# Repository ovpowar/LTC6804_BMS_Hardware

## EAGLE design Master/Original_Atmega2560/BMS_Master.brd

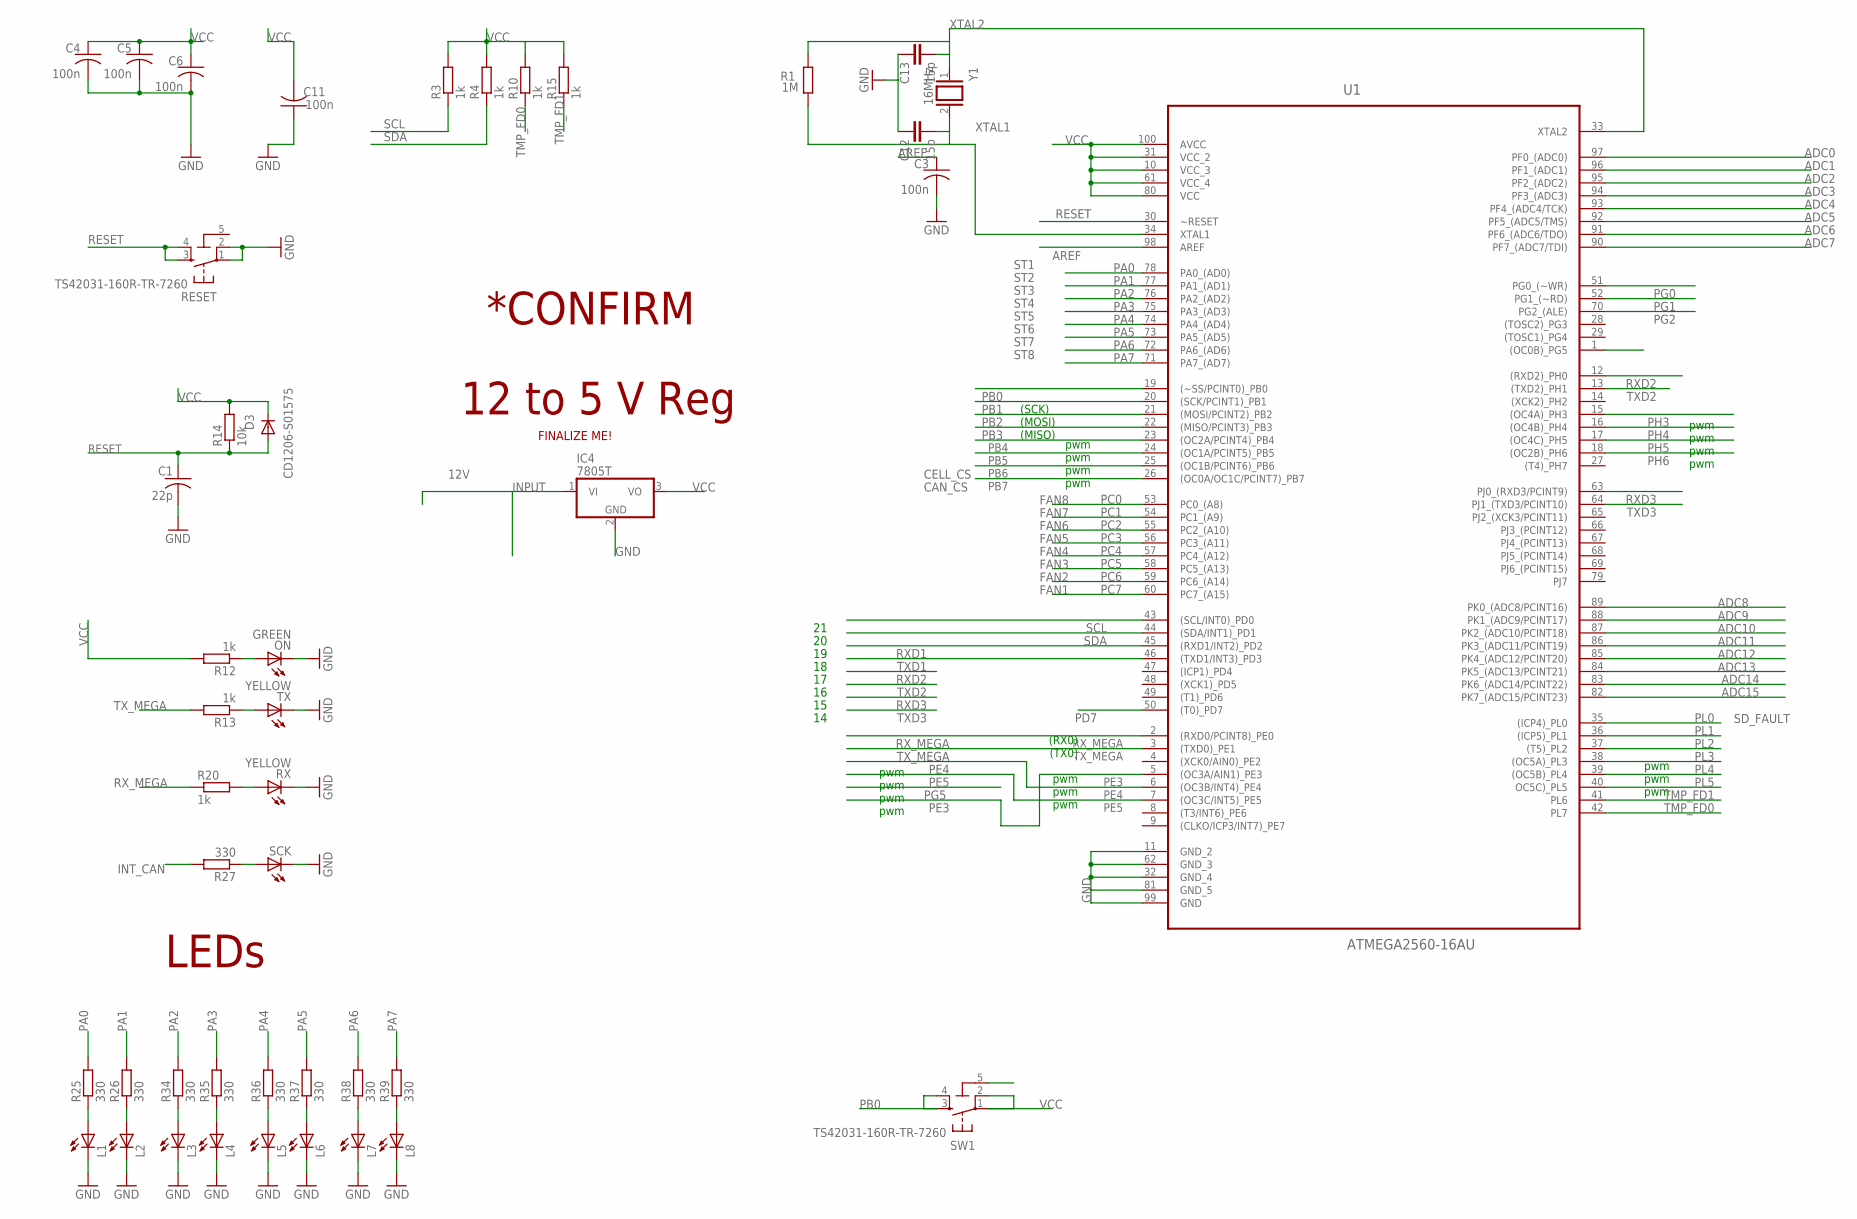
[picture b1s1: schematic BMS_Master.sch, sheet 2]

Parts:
C1: 22p; C1206
C3, C4, C5, C6, C11: 100n; C1206
C12, C13: 15p; C0603-ROUND
D3: CD1206-S01575; MINIMELF
IC4: 7805T; TO220H
L1, L2, L3, L4, L5, L6, L7, L8: LED_E; LED_1206
ON: GREEN; CHIP-LED0805
R1: 1M; R1206W
R3, R4, R10, R15: 1k; R1206
R12, R13, R20: 1k; R0603
R14: 10k; R1206
R25, R26, R27, R34, R35, R36, R37, R38, R39: 330; R0603
RESET: TS42031-160R-TR-7260; TS42
RX: YELLOW; CHIP-LED0805
SCK: LED_E; LED_1206
SW1: TS42031-160R-TR-7260; TS42
TX: YELLOW; CHIP-LED0805
U1: ATMEGA2560-16AU; QFP50P1600X1600X120-100N
Y1: 16MHz; QS

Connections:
5-GND: RESET.5 (5-GND)
ADC0: U1.97 (PF0_(ADC0))
ADC1: U1.96 (PF1_(ADC1))
ADC2: U1.95 (PF2_(ADC2))
ADC3: U1.94 (PF3_(ADC3))
ADC4: U1.93 (PF4_(ADC4/TCK))
ADC5: U1.92 (PF5_(ADC5/TMS))
ADC6: U1.91 (PF6_(ADC6/TDO))
ADC7: U1.90 (PF7_(ADC7/TDI))
ADC8: U1.89 (PK0_(ADC8/PCINT16))
ADC9: U1.88 (PK1_(ADC9/PCINT17))
ADC10: U1.87 (PK2_(ADC10/PCINT18))
ADC11: U1.86 (PK3_(ADC11/PCINT19))
ADC12: U1.85 (PK4_(ADC12/PCINT20))
ADC13: U1.84 (PK5_(ADC13/PCINT21))
ADC14: U1.83 (PK6_(ADC14/PCINT22))
ADC15: U1.82 (PK7_(ADC15/PCINT23))
AREF: C3.1, U1.98 (AREF)
GND: C1.2, C3.2, C4.2, C5.2, C6.2, C11.1, C12.1, C13.1, IC4.2 (GND), L1.C, L2.C, L3.C, L4.C, L5.C, L6.C, L7.C, L8.C, ON.C, RESET.1, RESET.2, RX.C, SCK.C, SW1.5 (5-GND), TX.C, U1.11 (GND_2), U1.32 (GND_4), U1.62 (GND_3), U1.81 (GND_5), U1.99 (GND); also elsewhere on the board
INPUT: IC4.1 (VI); also elsewhere on the board
INT_CAN: R27.2; also elsewhere on the board
unnamed: R20.2, RX.A
unnamed: R13.1, TX.A
unnamed: ON.A, R12.1
unnamed: R27.1, SCK.A
unnamed: L1.A, R25.1
unnamed: L2.A, R26.1
unnamed: L3.A, R34.1
unnamed: L4.A, R35.1
unnamed: L5.A, R36.1
unnamed: L6.A, R37.1
unnamed: L7.A, R38.1
unnamed: L8.A, R39.1
PA0: R25.2, U1.78 (PA0_(AD0))
PA1: R26.2, U1.77 (PA1_(AD1))
PA2: R34.2, U1.76 (PA2_(AD2))
PA3: R35.2, U1.75 (PA3_(AD3))
PA4: R36.2, U1.74 (PA4_(AD4))
PA5: R37.2, U1.73 (PA5_(AD5))
PA6: R38.2, U1.72 (PA6_(AD6))
PA7: R39.2, U1.71 (PA7_(AD7))
PB0: SW1.3, SW1.4, U1.19 ((~SS/PCINT0)_PB0)
PB1: U1.20 ((SCK/PCINT1)_PB1); also elsewhere on the board
PB2: U1.21 ((MOSI/PCINT2)_PB2); also elsewhere on the board
PB3: U1.22 ((MISO/PCINT3)_PB3); also elsewhere on the board
PB4: U1.23 ((OC2A/PCINT4)_PB4); also elsewhere on the board
PB5: U1.24 ((OC1A/PCINT5)_PB5); also elsewhere on the board
PB6: U1.25 ((OC1B/PCINT6)_PB6); also elsewhere on the board
PB7: U1.26 ((OC0A/OC1C/PCINT7)_PB7); also elsewhere on the board
PC0: U1.53 (PC0_(A8))
PC1: U1.54 (PC1_(A9))
PC2: U1.55 (PC2_(A10))
PC3: U1.56 (PC3_(A11))
PC4: U1.57 (PC4_(A12))
PC5: U1.58 (PC5_(A13))
PC6: U1.59 (PC6_(A14))
PC7: U1.60 (PC7_(A15))
PE3: U1.5 ((OC3A/AIN1)_PE3)
PE4: U1.6 ((OC3B/INT4)_PE4)
PE5: U1.7 ((OC3C/INT5)_PE5)
PG0: U1.51 (PG0_(~WR))
PG1: U1.52 (PG1_(~RD))
PG2: U1.70 (PG2_(ALE))
PG5: U1.1 ((OC0B)_PG5)
PH3: U1.15 ((OC4A)_PH3)
PH4: U1.16 ((OC4B)_PH4)
PH5: U1.17 ((OC4C)_PH5)
PH6: U1.18 ((OC2B)_PH6)
PL0: U1.35 ((ICP4)_PL0); also elsewhere on the board
PL1: U1.36 ((ICP5)_PL1); also elsewhere on the board
PL2: U1.37 ((T5)_PL2)
PL3: U1.38 ((OC5A)_PL3)
PL4: U1.39 ((OC5B)_PL4)
PL5: U1.40 (OC5C)_PL5)
RESET: C1.1, D3.A, R14.1, RESET.3, RESET.4, U1.30 (~RESET); also elsewhere on the board
RXD1: U1.45 ((RXD1/INT2)_PD2)
RXD2: U1.12 ((RXD2)_PH0)
RXD3: U1.63 (PJ0_(RXD3/PCINT9))
RX_MEGA: R20.1, U1.2 ((RXD0/PCINT8)_PE0); also elsewhere on the board
SCL: R3.1, U1.43 ((SCL/INT0)_PD0); also elsewhere on the board
SDA: R4.1, U1.44 ((SDA/INT1)_PD1); also elsewhere on the board
TMP_FD0: R10.1, U1.42 (PL7); also elsewhere on the board
TMP_FD1: R15.1, U1.41 (PL6); also elsewhere on the board
TXD1: U1.46 ((TXD1/INT3)_PD3)
TXD2: U1.13 ((TXD2)_PH1)
TXD3: U1.64 (PJ1_(TXD3/PCINT10))
TX_MEGA: R13.2, U1.3 ((TXD0)_PE1); also elsewhere on the board
VCC: C4.1, C5.1, C6.1, C11.2, D3.C, IC4.3 (VO), R3.2, R4.2, R10.2, R12.2, R14.2, R15.2, SW1.1, SW1.2, U1.10 (VCC_3), U1.31 (VCC_2), U1.61 (VCC_4), U1.80 (VCC), U1.100 (AVCC); also elsewhere on the board
XTAL1: C12.2, R1.1, U1.34 (XTAL1), Y1.2
XTAL2: C13.2, R1.2, U1.33 (XTAL2), Y1.1

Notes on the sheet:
pwm
(TX0)
(RX0)
(MISO)
(SCK)
(MOSI)
12 to 5 V Reg
CELL_CS
LEDs
CAN_CS
FINALIZE ME!
SD_FAULT
FAN1
FAN2
FAN3
FAN4
FAN7
FAN5
FAN6
FAN8
ST1
ST2
ST3
ST4
ST5
ST6
ST7
ST8
12V
*CONFIRM

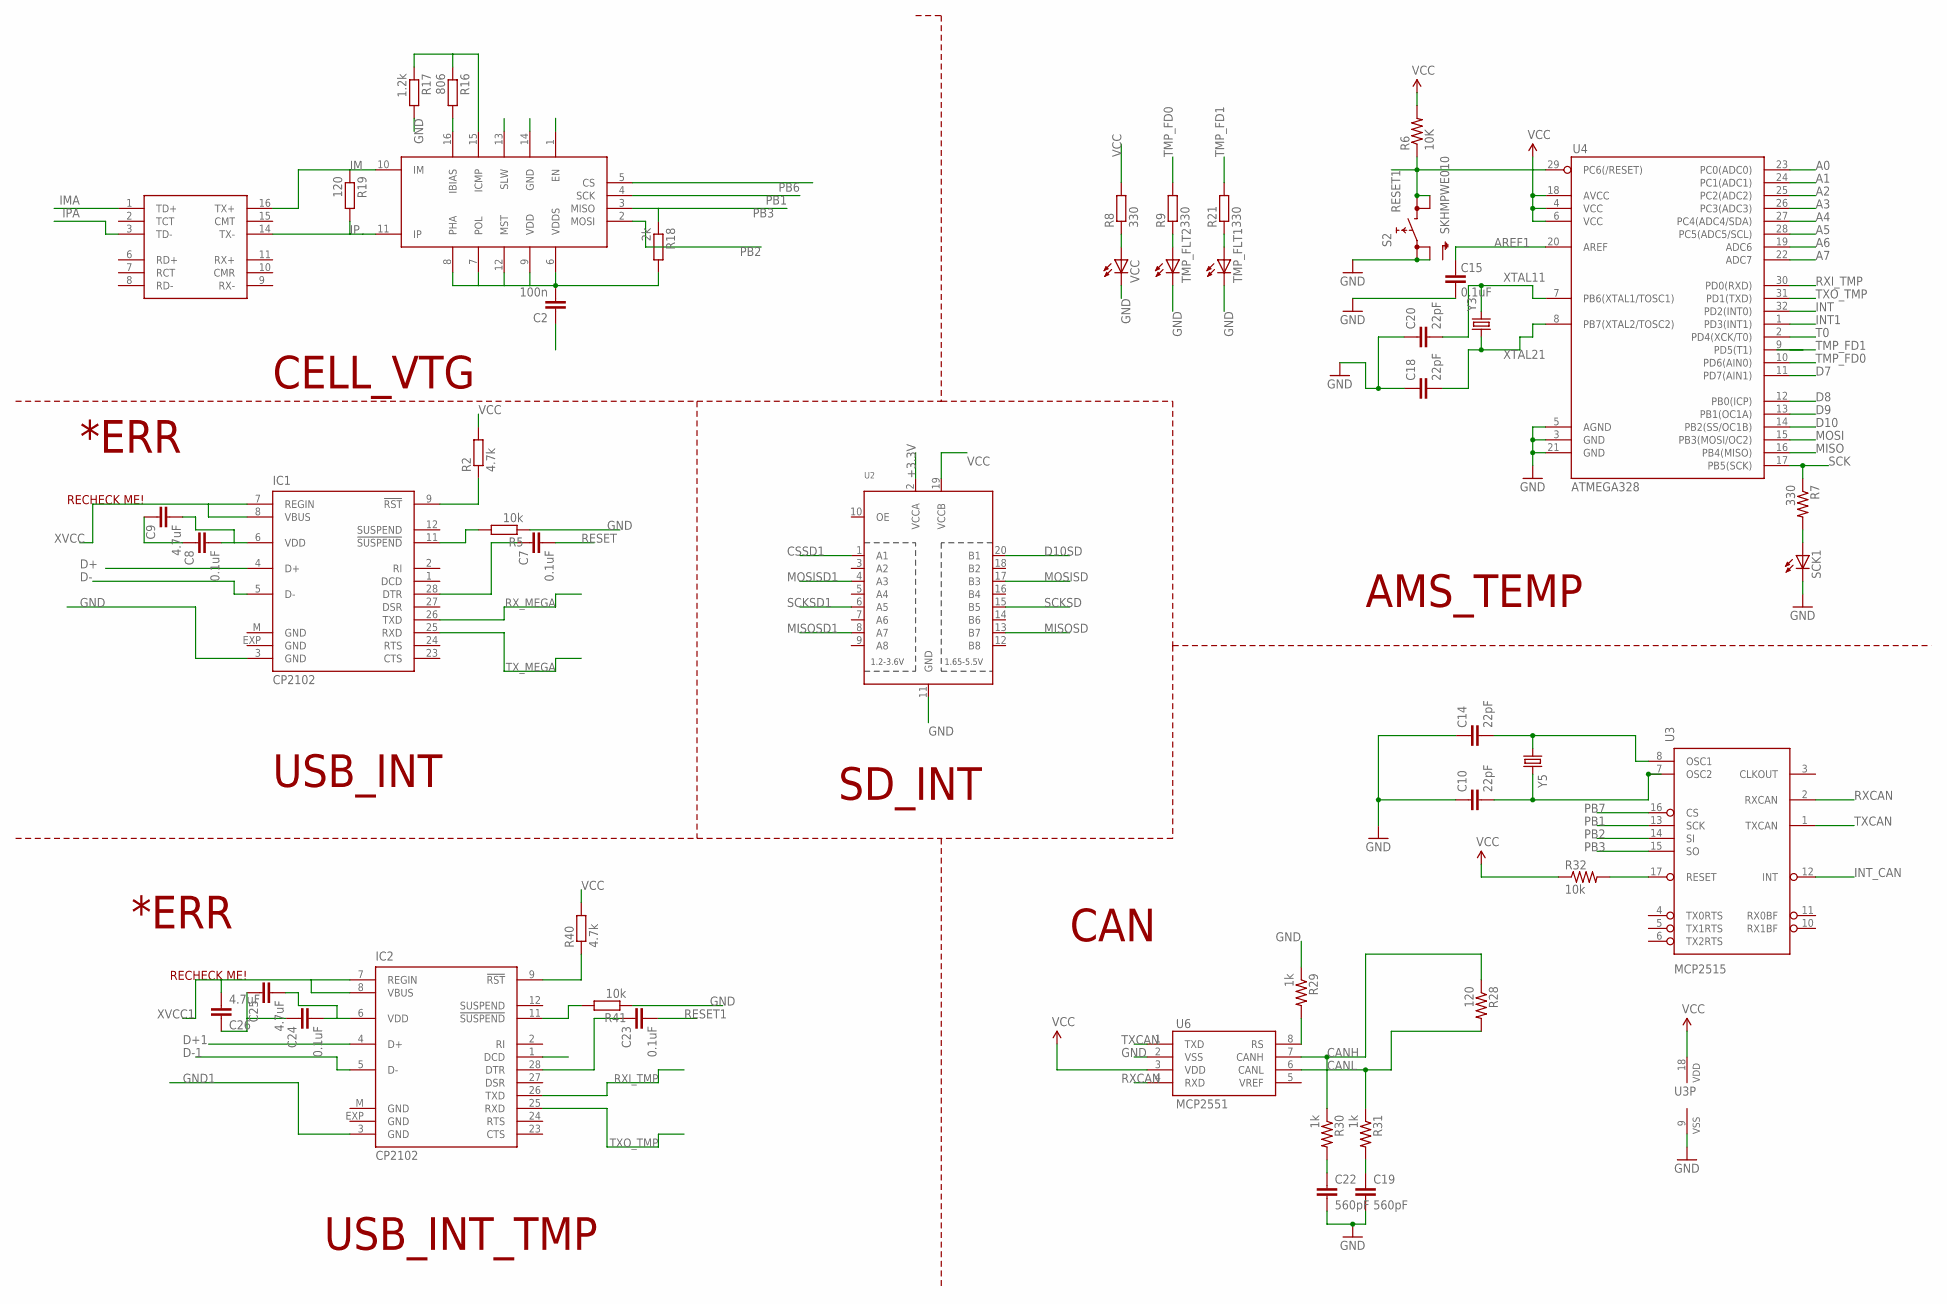
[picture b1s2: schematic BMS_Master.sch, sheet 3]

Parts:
C2: 100n; C1206
C7, C8, C23, C24: 0.1uF; C1206
C9, C25, C26: 4.7uF; C1206
C10, C14, C18, C20: 22pF; 1206
C15: 0.1uF; 1206
C19, C22: 560pF; 1206
IC1, IC2: CP2102; MLP28
R2, R40: 4.7k; R1206
R5, R41: 10k; R1206
R6: 10K; 1206
R7: 330; 0603-RES
R8, R9, R21: 330; R0603
R16: 806; R1206
R17: 1.2k; R1206
R18: 2k; R1206
R19: 120; R1206
R28: 120; 1206
R29, R30, R31: 1k; 1206
R32: 10k; 1206
S2: SKHMPWE010; SKHMPXE010
SCK1: LED_E; LED_1206
TMP_FLT1, TMP_FLT2: LED_E; LED_1206
U2: TXB0108PWR; TSSOP20
U3: MCP2515; SO-18W
U4: ATMEGA328; TQFP32-08
U6: MCP2551; SO08
U$3: LTC6820
U$4: HX1188N; HX1188
VCC: LED_E; LED_1206
Y3, Y5: CRYSTALHC49US; HC49US

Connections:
+3.3V: U2.2 (VCCA); also elsewhere on the board
A0: U4.23 (PC0(ADC0))
A1: U4.24 (PC1(ADC1))
A2: U4.25 (PC2(ADC2))
A3: U4.26 (PC3(ADC3))
A4: U4.27 (PC4(ADC4/SDA))
A5: U4.28 (PC5(ADC5/SCL))
A6: U4.19 (ADC6)
A7: U4.22 (ADC7)
AREF1: C15.2, U4.20 (AREF)
CANH: R28.1, R30.1, U6.7 (CANH); also elsewhere on the board
CANL: R28.2, R31.1, U6.6 (CANL); also elsewhere on the board
CSSD1: U2.1 (A1); also elsewhere on the board
D7: U4.11 (PD7(AIN1)); also elsewhere on the board
D8: U4.12 (PB0(ICP)); also elsewhere on the board
D9: U4.13 (PB1(OC1A)); also elsewhere on the board
D10: U4.14 (PB2(SS/OC1B)); also elsewhere on the board
D10SD: U2.20 (B1); also elsewhere on the board
D+: IC1.4 (D+); also elsewhere on the board
D+1: IC2.4 (D+); also elsewhere on the board
D-: IC1.5 (D-); also elsewhere on the board
D-1: IC2.5 (D-); also elsewhere on the board
GND: C2.1, C8.1, C9.1, C10.1, C14.1, C15.1, C18.1, C19.2, C20.1, C22.2, C24.1, C25.1, C26.1, IC1.3 (GND), IC1.EXP (GND), IC1.M (GND), IC2.EXP (GND), IC2.M (GND), R5.1, R17.2, R29.1, R41.1, S2.1 (1.1), S2.2 (1.2), SCK1.C, TMP_FLT1.C, TMP_FLT2.C, U2.11 (GND), U3.9 (VSS), U4.3 (GND), U4.5 (AGND), U4.21 (GND), U6.2 (VSS), U$3.1 (EN), U$3.13 (SLW), U$3.14 (GND), VCC.C; also elsewhere on the board
GND1: IC2.3 (GND)
IM: R19.1, U$3.10 (IM), U$4.16 (TX+)
IMA: U$4.1 (TD+); also elsewhere on the board
INT: U4.32 (PD2(INT0))
INT1: U4.1 (PD3(INT1))
INT_CAN: U3.12 (INT); also elsewhere on the board
IP: R19.2, U$3.11 (IP), U$4.14 (TX-)
IPA: U$4.3 (TD-); also elsewhere on the board
MISO: U4.16 (PB4(MISO)); also elsewhere on the board
MISOSD: U2.13 (B7); also elsewhere on the board
MISOSD1: U2.8 (A7); also elsewhere on the board
MOSI: U4.15 (PB3(MOSI/OC2)); also elsewhere on the board
MOSISD: U2.17 (B3); also elsewhere on the board
MOSISD1: U2.4 (A3); also elsewhere on the board
unnamed: C14.2, U3.8 (OSC1), Y5.1
unnamed: C10.2, U3.7 (OSC2), Y5.2
unnamed: R16.2, U$3.16 (IBIAS)
unnamed: R16.1, R17.1, U$3.15 (ICMP)
unnamed: R29.2, U6.8 (RS)
unnamed: C22.1, R30.2
unnamed: C19.1, R31.2
unnamed: C7.1, IC1.28 (DTR)
unnamed: IC1.11 (!SUSPEND), R5.2
unnamed: C8.2, C9.2, IC1.6 (VDD)
unnamed: IC1.9 (!RST), R2.1
unnamed: R32.2, U3.17 (RESET)
unnamed: R7.2, SCK1.A
unnamed: R8.1, VCC.A
unnamed: R9.1, TMP_FLT2.A
unnamed: R21.1, TMP_FLT1.A
unnamed: C23.1, IC2.28 (DTR)
unnamed: C24.2, C25.2, IC2.6 (VDD)
unnamed: IC2.9 (!RST), R40.1
unnamed: IC2.11 (!SUSPEND), R41.2
PB1: U3.13 (SCK), U$3.4 (SCK); also elsewhere on the board
PB2: U3.14 (SI), U$3.2 (MOSI); also elsewhere on the board
PB3: R18.1, U3.15 (SO), U$3.3 (MISO); also elsewhere on the board
PB6: U$3.5 (CS); also elsewhere on the board
PB7: U3.16 (CS); also elsewhere on the board
RESET: C7.2; also elsewhere on the board
RESET1: C23.2, R6.1, S2.3 (2.1), S2.4 (2.2), U4.29 (PC6(/RESET)); also elsewhere on the board
RXCAN: U3.2 (RXCAN), U6.4 (RXD)
RXI_TMP: IC2.26 (TXD), U4.30 (PD0(RXD)); also elsewhere on the board
RX_MEGA: IC1.26 (TXD); also elsewhere on the board
SCK: R7.1, U4.17 (PB5(SCK)); also elsewhere on the board
SCKSD: U2.15 (B5); also elsewhere on the board
SCKSD1: U2.6 (A5); also elsewhere on the board
T0: U4.2 (PD4(XCK/T0))
TMP_FD0: R9.2, U4.10 (PD6(AIN0)); also elsewhere on the board
TMP_FD1: R21.2, U4.9 (PD5(T1)); also elsewhere on the board
TXCAN: U3.1 (TXCAN), U6.1 (TXD)
TXO_TMP: IC2.25 (RXD), U4.31 (PD1(TXD)); also elsewhere on the board
TX_MEGA: IC1.25 (RXD); also elsewhere on the board
VCC: C2.2, R2.2, R6.2, R8.2, R18.2, R32.1, R40.2, U2.19 (VCCB), U3.18 (VDD), U4.4 (VCC), U4.6 (VCC), U4.18 (AVCC), U6.3 (VDD), U$3.6 (VDDS), U$3.7 (POL), U$3.8 (PHA), U$3.9 (VDD), U$3.12 (MST); also elsewhere on the board
XTAL11: C20.2, U4.7 (PB6(XTAL1/TOSC1)), Y3.2
XTAL21: C18.2, U4.8 (PB7(XTAL2/TOSC2)), Y3.1
XVCC: IC1.7 (REGIN), IC1.8 (VBUS); also elsewhere on the board
XVCC1: C26.2, IC2.7 (REGIN), IC2.8 (VBUS); also elsewhere on the board

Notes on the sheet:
RECHECK ME!
CELL_VTG
USB_INT
AMS_TEMP
SD_INT
CAN
USB_INT_TMP
*ERR

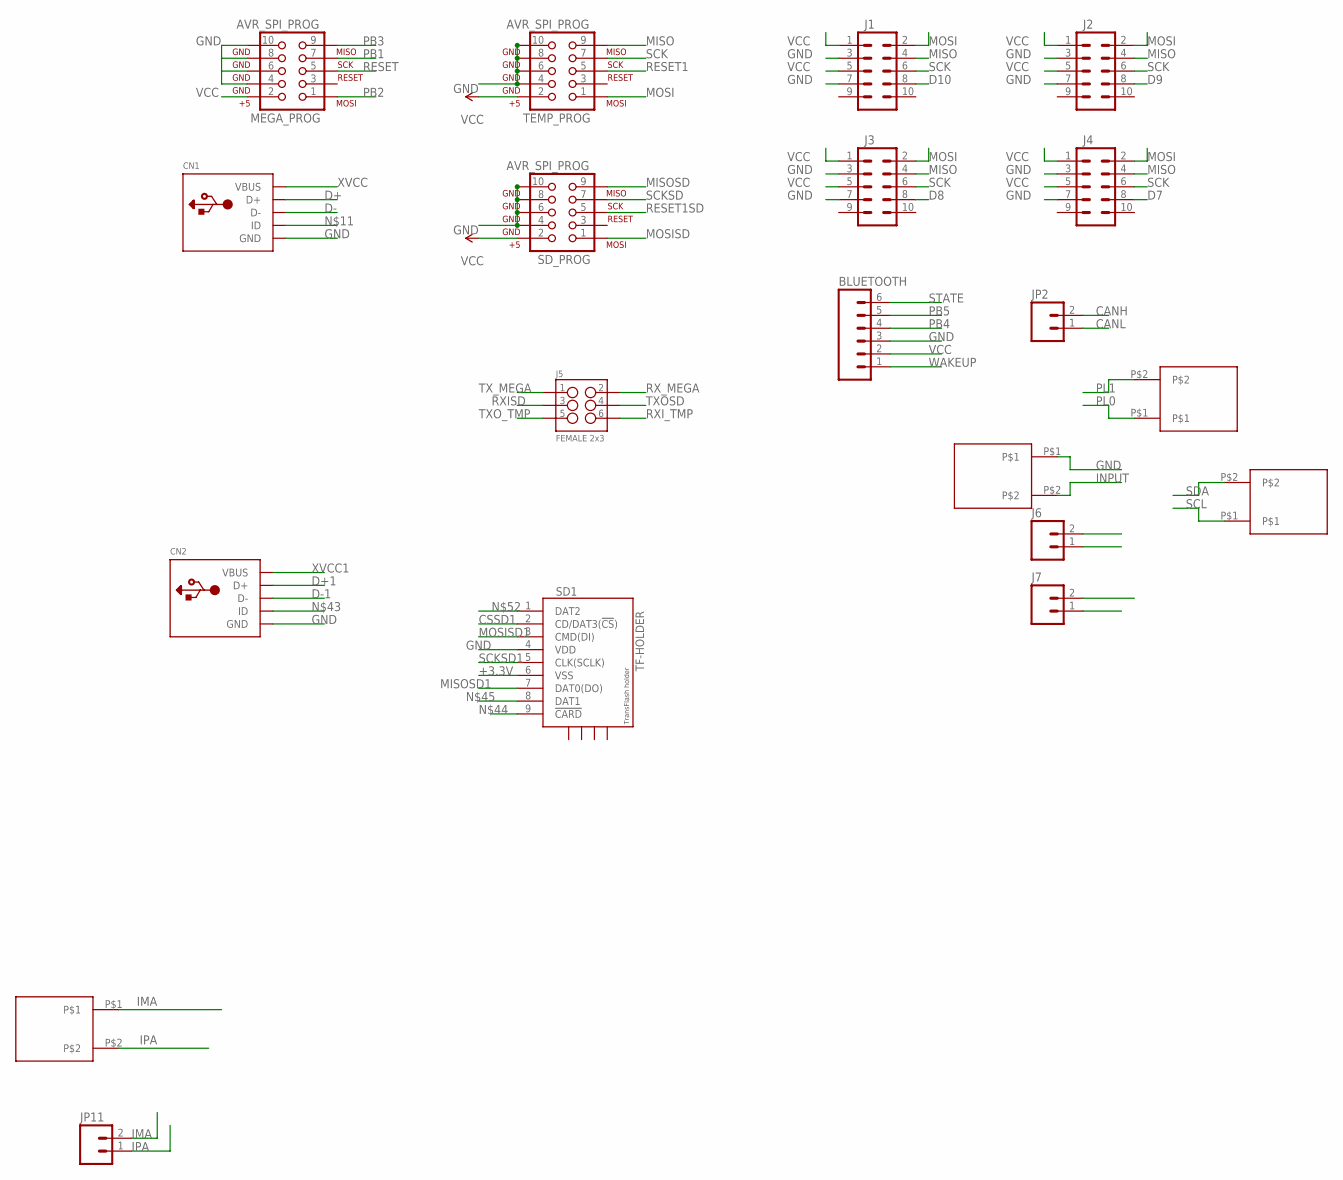
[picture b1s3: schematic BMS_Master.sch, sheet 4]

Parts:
BLUETOOTH: M06SILK_FEMALE_PTH; 1X06
CN1, CN2: USBMINIB; USB-MINIB
J1, J2, J3, J4: M05X2PTH; AVR_ICSP
J5: FEMALE 2x3; 2X3
J6, J7: M02PTH; 1X02
JP2: M02JST-PTH-2; JST-2-PTH
JP11: M02PTH; 1X02
MEGA_PROG: AVR_SPI_PROG; AVR_ICSP
SD1: TF-HOLDER; TF-PULL
SD_PROG: AVR_SPI_PROG; AVR_ICSP
TEMP_PROG: AVR_SPI_PROG; AVR_ICSP
U$1, U$5, U$6, U$7: MOLEX_2_PIN; MOLEX_2PIN

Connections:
+3.3V: SD1.6 (VSS); also elsewhere on the board
CANH: JP2.2; also elsewhere on the board
CANL: JP2.1; also elsewhere on the board
CSSD1: SD1.2 (CD/DAT3(!CS!)); also elsewhere on the board
D7: J4.8; also elsewhere on the board
D8: J3.8; also elsewhere on the board
D9: J2.8; also elsewhere on the board
D10: J1.8; also elsewhere on the board
D+: CN1.D+; also elsewhere on the board
D+1: CN2.D+; also elsewhere on the board
D-: CN1.D-; also elsewhere on the board
D-1: CN2.D-; also elsewhere on the board
GND: BLUETOOTH.3, CN1.GND, CN2.GND, J1.3, J1.7, J2.3, J2.7, J3.3, J3.7, J4.3, J4.7, MEGA_PROG.4, MEGA_PROG.6, MEGA_PROG.8, MEGA_PROG.10, SD1.4 (VDD), SD_PROG.4, SD_PROG.6, SD_PROG.8, SD_PROG.10, TEMP_PROG.4, TEMP_PROG.6, TEMP_PROG.8, TEMP_PROG.10, U$6.P$1; also elsewhere on the board
IMA: JP11.2, U$5.P$1; also elsewhere on the board
INPUT: U$6.P$2; also elsewhere on the board
IPA: JP11.1, U$5.P$2; also elsewhere on the board
MISO: J1.4, J2.4, J3.4, J4.4, TEMP_PROG.9; also elsewhere on the board
MISOSD: SD_PROG.9; also elsewhere on the board
MISOSD1: SD1.7 (DAT0(DO)); also elsewhere on the board
MOSI: J1.2, J2.2, J3.2, J4.2, TEMP_PROG.1; also elsewhere on the board
MOSISD: SD_PROG.1; also elsewhere on the board
MOSISD1: SD1.3 (CMD(DI)); also elsewhere on the board
PB1: MEGA_PROG.7; also elsewhere on the board
PB2: MEGA_PROG.1; also elsewhere on the board
PB3: MEGA_PROG.9; also elsewhere on the board
PB4: BLUETOOTH.4; also elsewhere on the board
PB5: BLUETOOTH.5; also elsewhere on the board
PL0: U$7.P$1; also elsewhere on the board
PL1: U$7.P$2; also elsewhere on the board
RESET: MEGA_PROG.5; also elsewhere on the board
RESET1: TEMP_PROG.5; also elsewhere on the board
RESET1SD: SD_PROG.5; also elsewhere on the board
RXISD: J5.3; also elsewhere on the board
RXI_TMP: J5.6; also elsewhere on the board
RX_MEGA: J5.2; also elsewhere on the board
SCK: J1.6, J2.6, J3.6, J4.6, TEMP_PROG.7; also elsewhere on the board
SCKSD: SD_PROG.7; also elsewhere on the board
SCKSD1: SD1.5 (CLK(SCLK)); also elsewhere on the board
SCL: U$1.P$1; also elsewhere on the board
SDA: U$1.P$2; also elsewhere on the board
STATE: BLUETOOTH.6
TXOSD: J5.4; also elsewhere on the board
TXO_TMP: J5.5; also elsewhere on the board
TX_MEGA: J5.1; also elsewhere on the board
VCC: BLUETOOTH.2, J1.1, J1.5, J2.1, J2.5, J3.1, J3.5, J4.1, J4.5, J6.1, J7.1, MEGA_PROG.2, SD_PROG.2, TEMP_PROG.2; also elsewhere on the board
WAKEUP: BLUETOOTH.1
XVCC: CN1.VBUS, J6.2; also elsewhere on the board
XVCC1: CN2.VBUS, J7.2; also elsewhere on the board

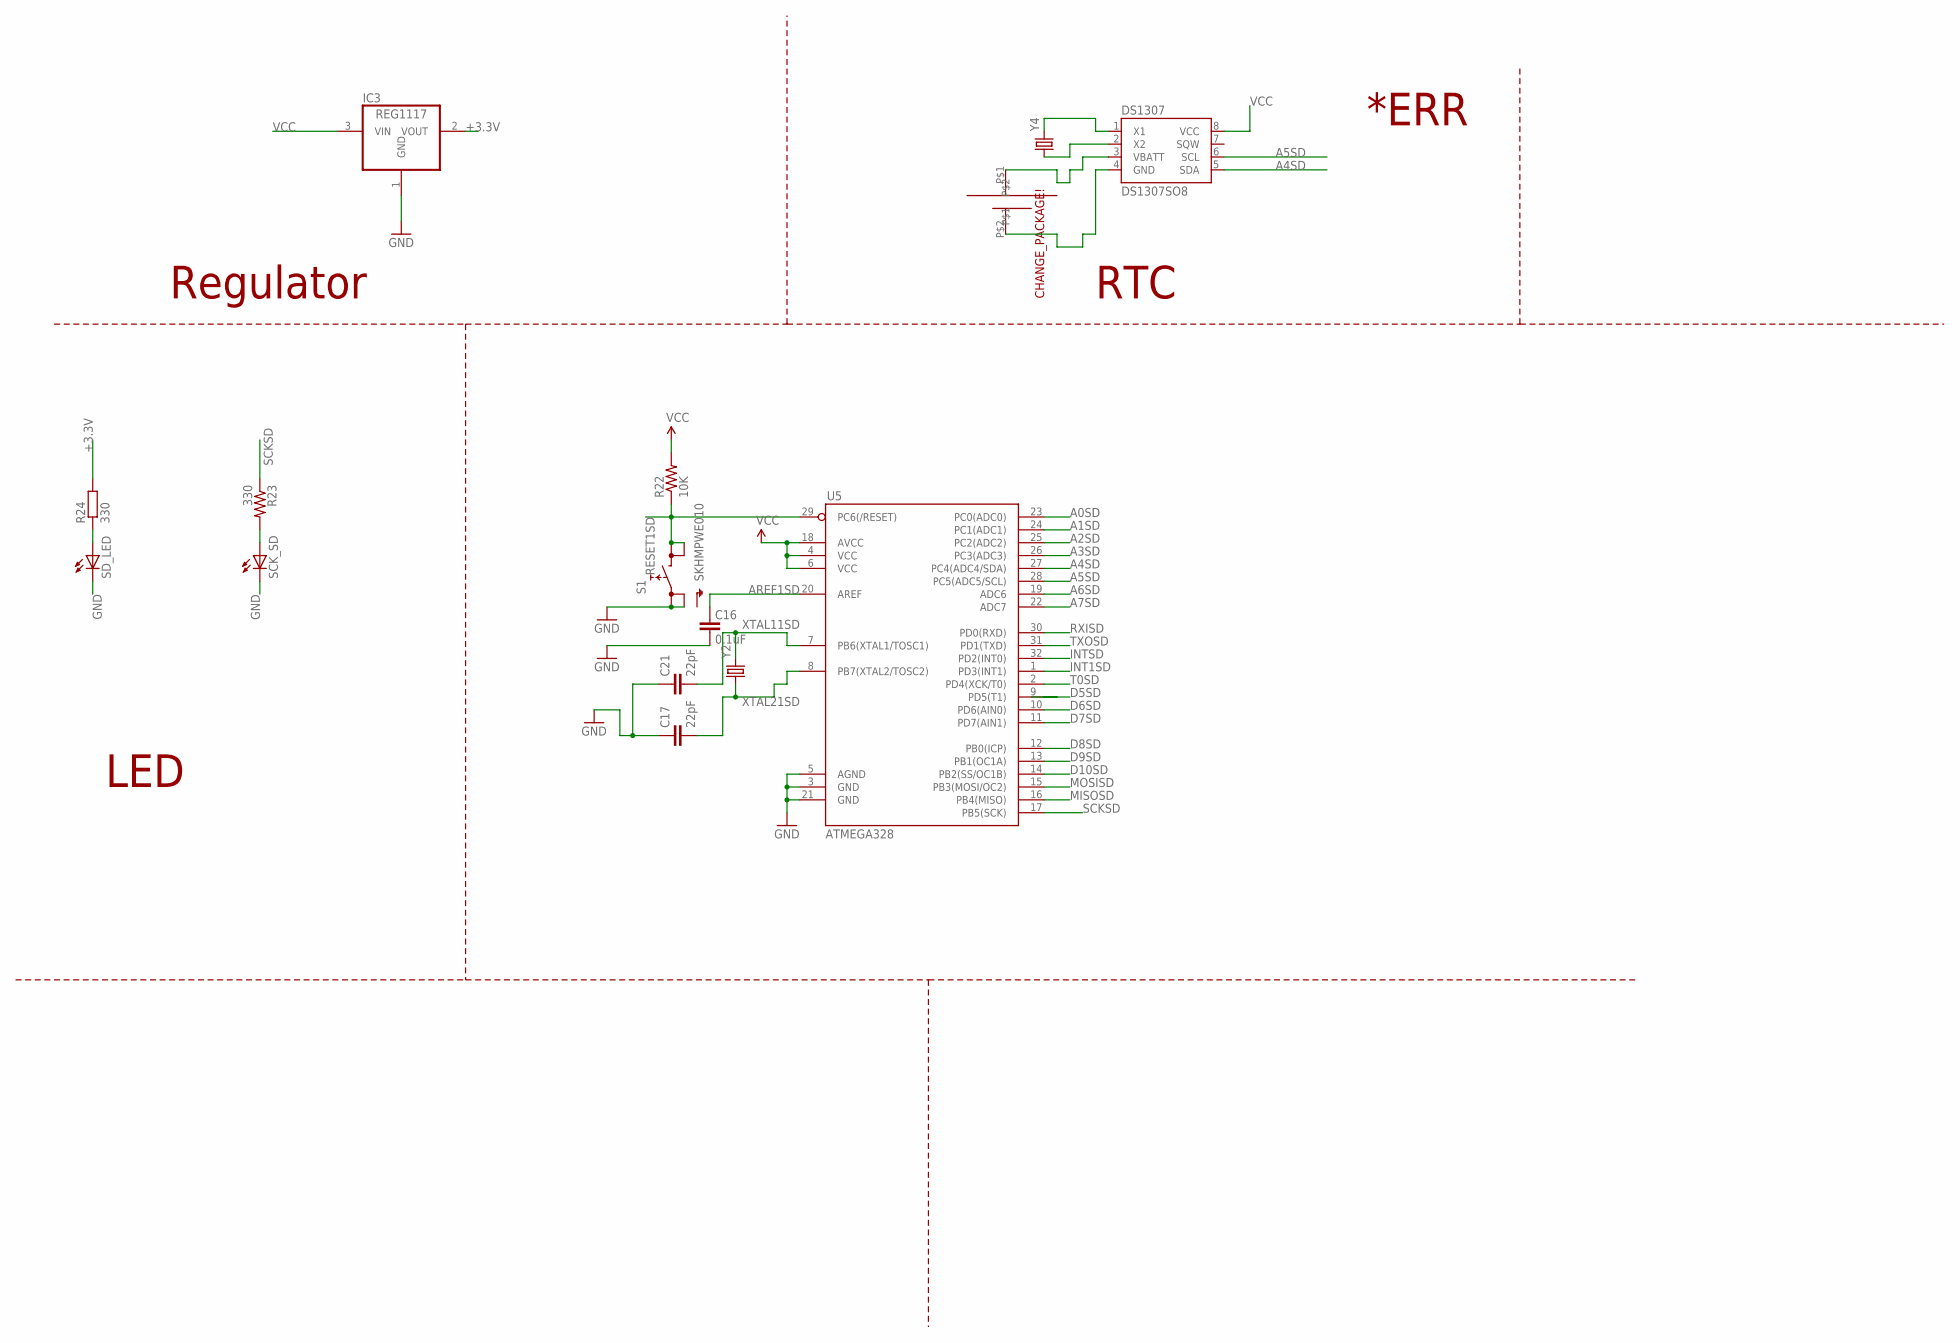
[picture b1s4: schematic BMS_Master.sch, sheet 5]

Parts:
C16: 0.1uF; 1206
C17, C21: 22pF; 1206
CR2032: CR2032
DS1307: DS1307SO8; SO08
IC3: REG1117; SOT223
R22: 10K; 1206
R23: 330; 1206
R24: 330; R1206
S1: SKHMPWE010; SKHMPXE010
SCK_SD: LED_E; LED_1206
SD_LED: LED_E; LED_1206
U5: ATMEGA328; TQFP32-08
Y2: CRYSTALHC49US; HC49US
Y4: CRYSTAL32-SMD; CRYSTAL-32KHZ-SMD

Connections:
+3.3V: IC3.2 (VOUT), R24.2; also elsewhere on the board
A0SD: U5.23 (PC0(ADC0))
A1SD: U5.24 (PC1(ADC1))
A2SD: U5.25 (PC2(ADC2))
A3SD: U5.26 (PC3(ADC3))
A4SD: DS1307.5 (SDA), U5.27 (PC4(ADC4/SDA))
A5SD: DS1307.6 (SCL), U5.28 (PC5(ADC5/SCL))
A6SD: U5.19 (ADC6)
A7SD: U5.22 (ADC7)
AREF1SD: C16.2, U5.20 (AREF)
D5SD: U5.9 (PD5(T1))
D6SD: U5.10 (PD6(AIN0))
D7SD: U5.11 (PD7(AIN1))
D8SD: U5.12 (PB0(ICP))
D9SD: U5.13 (PB1(OC1A))
D10SD: U5.14 (PB2(SS/OC1B)); also elsewhere on the board
GND: C16.1, C17.1, C21.1, IC3.1 (GND), S1.1 (1.1), S1.2 (1.2), SCK_SD.C, SD_LED.C, U5.3 (GND), U5.5 (AGND), U5.21 (GND); also elsewhere on the board
INT1SD: U5.1 (PD3(INT1))
INTSD: U5.32 (PD2(INT0))
MISOSD: U5.16 (PB4(MISO)); also elsewhere on the board
MOSISD: U5.15 (PB3(MOSI/OC2)); also elsewhere on the board
unnamed: DS1307.1 (X1), Y4.X2 (2)
unnamed: DS1307.2 (X2), Y4.X1 (1)
unnamed: CR2032.P$2, DS1307.4 (GND)
unnamed: R23.2, SCK_SD.A
unnamed: R24.1, SD_LED.A
unnamed: CR2032.P$1, DS1307.3 (VBATT)
RESET1SD: R22.1, S1.3 (2.1), S1.4 (2.2), U5.29 (PC6(/RESET)); also elsewhere on the board
RXISD: U5.30 (PD0(RXD)); also elsewhere on the board
SCKSD: R23.1, U5.17 (PB5(SCK)); also elsewhere on the board
T0SD: U5.2 (PD4(XCK/T0))
TXOSD: U5.31 (PD1(TXD)); also elsewhere on the board
VCC: DS1307.8 (VCC), IC3.3 (VIN), R22.2, U5.4 (VCC), U5.6 (VCC), U5.18 (AVCC); also elsewhere on the board
XTAL11SD: C21.2, U5.7 (PB6(XTAL1/TOSC1)), Y2.2
XTAL21SD: C17.2, U5.8 (PB7(XTAL2/TOSC2)), Y2.1

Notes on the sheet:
LED
Regulator
RTC
CHANGE_PACKAGE!
*ERR

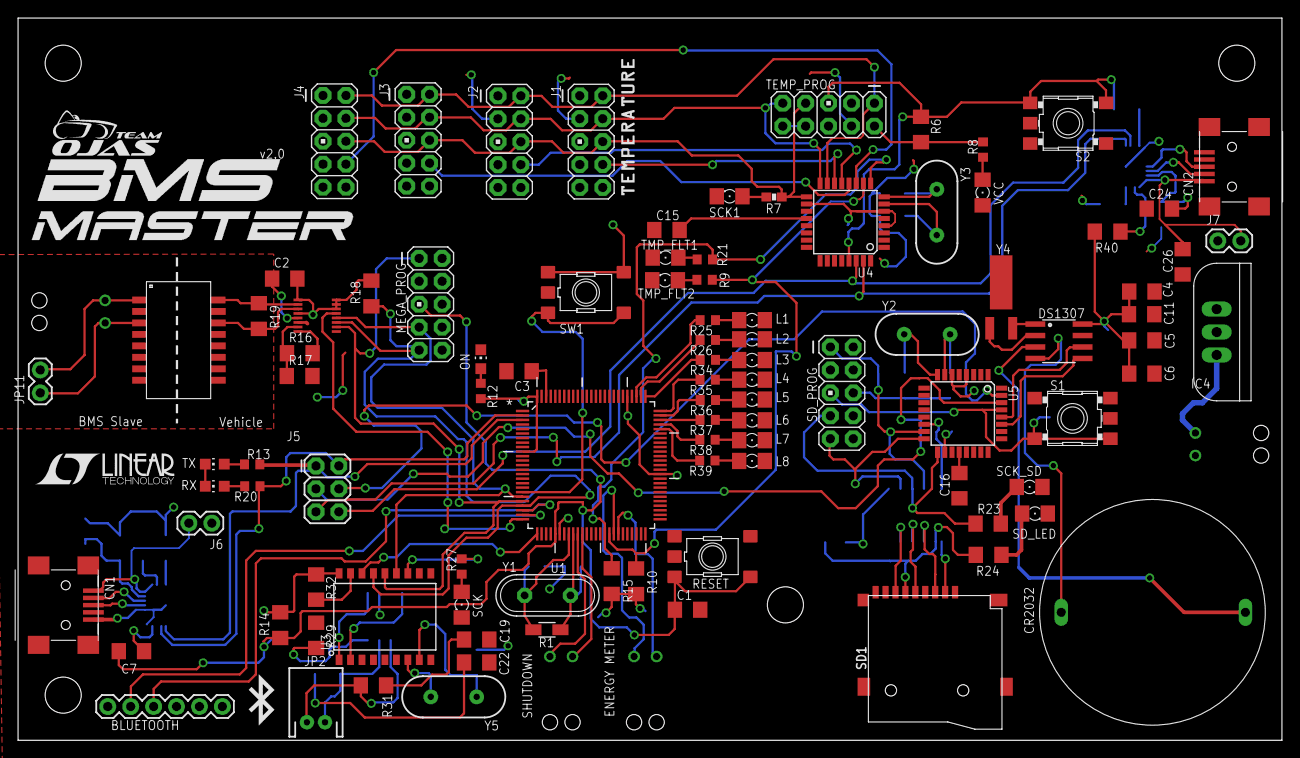
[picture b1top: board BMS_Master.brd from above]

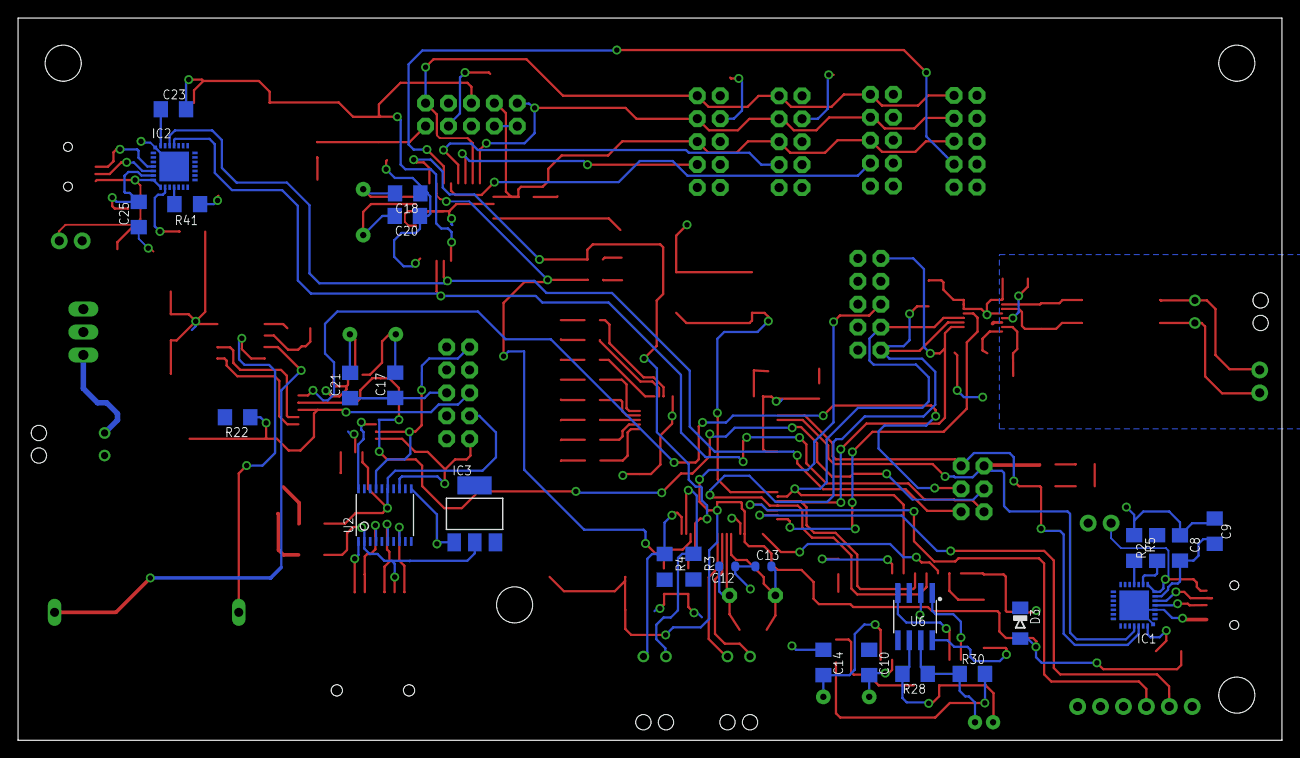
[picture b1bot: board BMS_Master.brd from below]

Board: 2 copper layers, 140.0 x 80.0 mm, 127 parts (26 on the bottom side), 114 nets.

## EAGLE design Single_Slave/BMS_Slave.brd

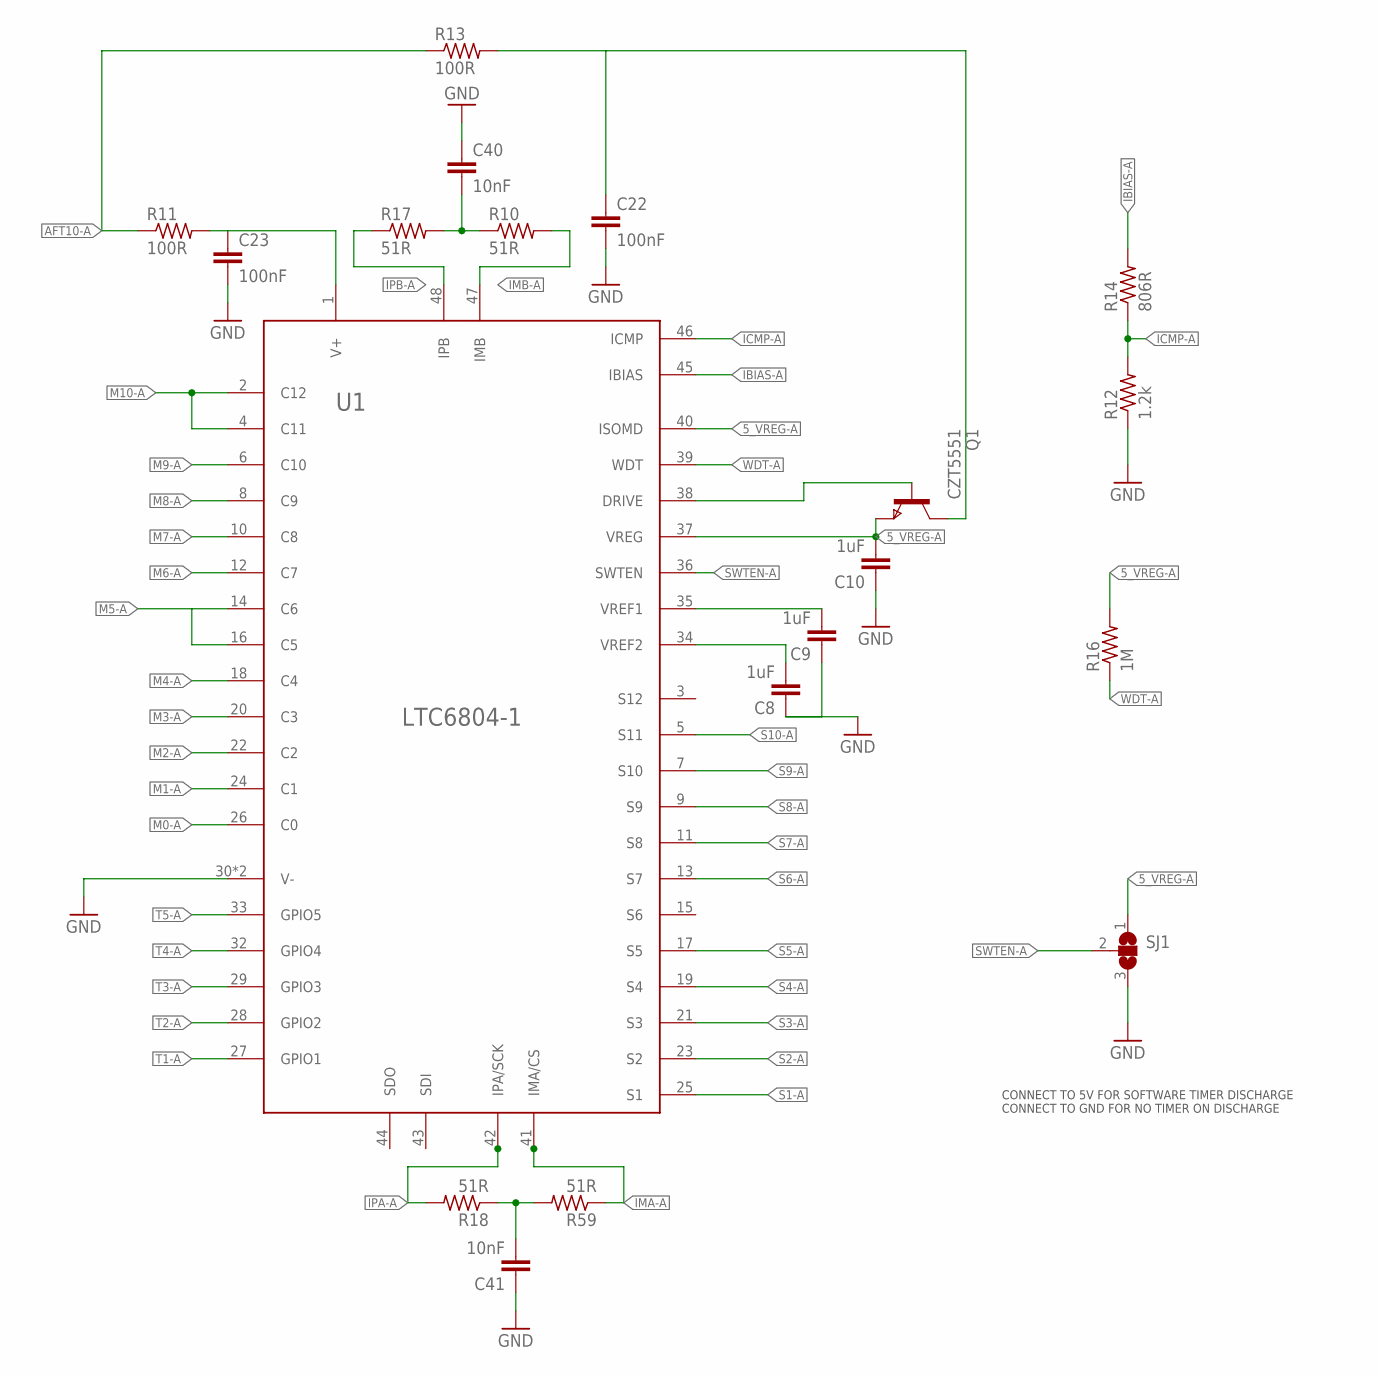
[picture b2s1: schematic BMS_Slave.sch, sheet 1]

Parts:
C8, C9, C10: 1uF; 0603
C22, C23: 100nF; 0805
C40, C41: 10nF; 0805
Q1: CZT5551; SOT223
R10, R17, R18, R59: 51R; 0603
R11, R13: 100R; 0603
R12: 1.2k; 0603
R14: 806R; 0603
R16: 1M; 0603
SJ1: SJ2W; SJ_2
U1: LTC6804; 48-LEAD_SSOP

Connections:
5_VREG-A: C10.P$2 (2), Q1.3 (E), R16.P$2 (2), SJ1.1, U1.37 (VREG), U1.40 (ISOMD); also elsewhere on the board
AFT10-A: R11.P$1 (1), R13.P$1 (1); also elsewhere on the board
GNDA: C8.P$1 (1), C9.P$1 (1), C10.P$1 (1), C22.P$2 (2), C23.P$2 (2), C40.P$1 (1), C41.P$1 (1), R12.P$1 (1), SJ1.3, U1.30 (V-), U1.31 (V-); also elsewhere on the board
IBIAS-A: R14.P$2 (2), U1.45 (IBIAS)
ICMP-A: R12.P$2 (2), R14.P$1 (1), U1.46 (ICMP)
IMA-A: R59.P$1 (1), U1.41 (IMA/CS); also elsewhere on the board
IMB-A: R10.P$2 (2), U1.47 (IMB); also elsewhere on the board
IPA-A: R18.P$2 (2), U1.42 (IPA/SCK); also elsewhere on the board
IPB-A: R17.P$1 (1), U1.48 (IPB); also elsewhere on the board
M0-A: U1.26 (C0); also elsewhere on the board
M1-A: U1.24 (C1); also elsewhere on the board
M2-A: U1.22 (C2); also elsewhere on the board
M3-A: U1.20 (C3); also elsewhere on the board
M4-A: U1.18 (C4); also elsewhere on the board
M5-A: U1.14 (C6), U1.16 (C5); also elsewhere on the board
M6-A: U1.12 (C7); also elsewhere on the board
M7-A: U1.10 (C8); also elsewhere on the board
M8-A: U1.8 (C9); also elsewhere on the board
M9-A: U1.6 (C10); also elsewhere on the board
M10-A: U1.2 (C12), U1.4 (C11); also elsewhere on the board
unnamed: C9.P$2 (2), U1.35 (VREF1)
unnamed: C8.P$2 (2), U1.34 (VREF2)
unnamed: C40.P$2 (2), R10.P$1 (1), R17.P$2 (2)
unnamed: C41.P$2 (2), R18.P$1 (1), R59.P$2 (2)
unnamed: Q1.1 (B), U1.38 (DRIVE)
unnamed: C22.P$1 (1), Q1.2 (C), Q1.4 (C), R13.P$2 (2)
unnamed: C23.P$1 (1), R11.P$2 (2), U1.1 (V+)
S1-A: U1.25 (S1); also elsewhere on the board
S2-A: U1.23 (S2); also elsewhere on the board
S3-A: U1.21 (S3); also elsewhere on the board
S4-A: U1.19 (S4); also elsewhere on the board
S5-A: U1.17 (S5); also elsewhere on the board
S6-A: U1.13 (S7); also elsewhere on the board
S7-A: U1.11 (S8); also elsewhere on the board
S8-A: U1.9 (S9); also elsewhere on the board
S9-A: U1.7 (S10); also elsewhere on the board
S10-A: U1.5 (S11); also elsewhere on the board
SWTEN-A: SJ1.2, U1.36 (SWTEN)
T1-A: U1.27 (GPIO1); also elsewhere on the board
T2-A: U1.28 (GPIO2); also elsewhere on the board
T3-A: U1.29 (GPIO3); also elsewhere on the board
T4-A: U1.32 (GPIO4); also elsewhere on the board
T5-A: U1.33 (GPIO5); also elsewhere on the board
WDT-A: R16.P$1 (1), U1.39 (WDT)

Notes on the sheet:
CONNECT TO 5V FOR SOFTWARE TIMER DISCHARGE CONNECT TO GND FOR NO TIMER ON DISCHARGE

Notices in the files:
parts and their libraries:
SparkFun-Connectors: Licensing: Creative Commons ShareAlike 4.0 International - https://creativecommons.org/licenses/by-sa/4.0
SparkFun-Passives: Licensing: CC v3.0 Share-Alike You are welcome to use this library for commercial purposes.
